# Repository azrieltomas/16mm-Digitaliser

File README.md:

# 16mm Digitaliser
A slight improvement on the [8mm Digitaliser](https://github.com/azrieltomas/8mm-Digitaliser)
This is currently a work in progress and not fully implemented.

### Design
The hardware design to capture the frames utilises a constantly running motor, and dual IR sensors to determine when sprocket perforations have passed.
As 5+ frames can fit on the digital capture, photographs are taken every 5 frames. Cropping will be acheived by automatically offsetting the crop zone and exporting to separate images.

### Parts
Parts for aligning the film and holding the sensors are from various 3D prints.

\
*Physical Parts Layout (FreeCAD)*

### Controller
Each perforation sensor has two fine tuning methods:
* Gain (affects sensor output level)
* Cutoff (affects reference level).
The gain and cutoff signals are compared with an LM741 to determine if a perforation is sensed.This is adjustable to compensate for light sections along the film edge that are not perforations, but are still picked up by the sensor.Both perforation sensors are connected by an AND gate to a counter to further filter out non-perforations on single sides of the film.

For single perforation film, a switch sets the sense2 output to always on.

Once the counter has reaches four, it triggers the camera, and resets on five via an AND gate on QA and QC.

The motor can be switched on/off via a buffer circuit. I have used a BUL128 only because I have spares, and they're the only transistor on hand that can handle the motor current. It is probably wise to put a flyback diode on the motor.

\
*Controller Design (KiCAD)*

### Audio
Audio is captured in two ways, depending on the storage method.
Digital processing can be done by any additional system.

#### Standard magnetic audio
Audio is picked up by a modified cassette tape head and amplified by an LM386 for simplicity.

#### Movietone
Audio is converted by an IR phototransistor - theoretically the same one used for the second set of perforations in dual perf film.
A BC547 amplifier boosts this to line levels.

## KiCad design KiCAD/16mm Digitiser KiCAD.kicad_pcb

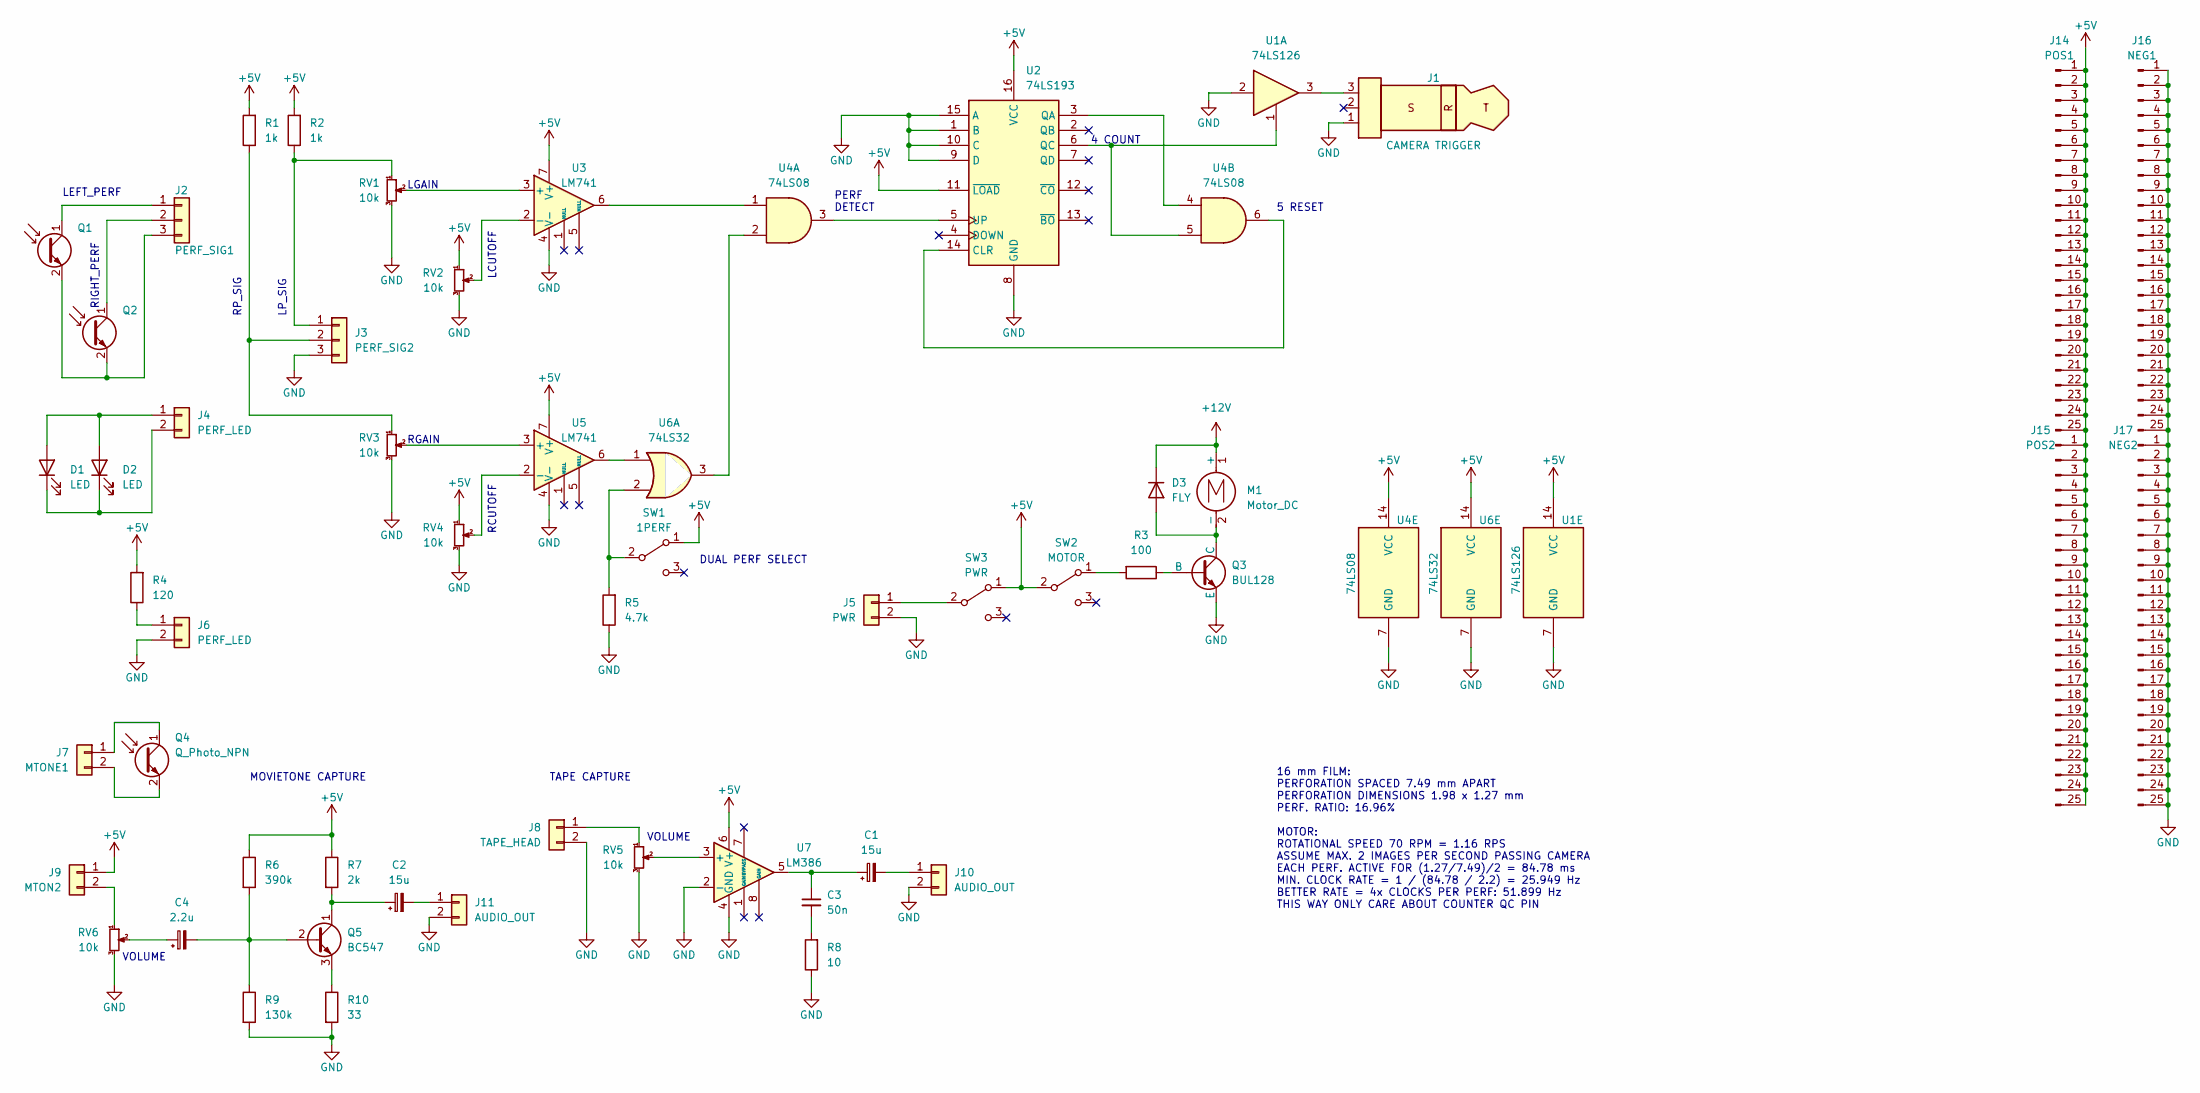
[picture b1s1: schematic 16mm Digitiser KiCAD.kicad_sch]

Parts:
C1, C2: 15u; C_Radial_D6.3mm_H5.0mm_P2.50mm
C3: 50n; C_Rect_L4.6mm_W2.0mm_P2.50mm_MKS02_FKP02
C4: 2.2u; C_Radial_D6.3mm_H5.0mm_P2.50mm
D1, D2: LED; LED_D5.0mm
D3: FLY
J1: CAMERA TRIGGER; JST_EH_B3B-EH-A_1x03_P2.50mm_Vertical
J2: PERF_SIG1; JST_EH_B3B-EH-A_1x03_P2.50mm_Vertical
J3: PERF_SIG2; JST_EH_B3B-EH-A_1x03_P2.50mm_Vertical
J4, J6: PERF_LED; JST_EH_B2B-EH-A_1x02_P2.50mm_Vertical
J5: PWR; JST_EH_B2B-EH-A_1x02_P2.50mm_Vertical
J7: MTONE1; JST_EH_B2B-EH-A_1x02_P2.50mm_Vertical
J8: TAPE_HEAD; JST_EH_B2B-EH-A_1x02_P2.50mm_Vertical
J9: MTON2; JST_EH_B2B-EH-A_1x02_P2.50mm_Vertical
J10, J11: AUDIO_OUT; JST_EH_B2B-EH-A_1x02_P2.50mm_Vertical
J14: POS1; PinHeader_1x25_P2.54mm_Vertical
J15: POS2; PinHeader_1x25_P2.54mm_Vertical
J16: NEG1; PinHeader_1x25_P2.54mm_Vertical
J17: NEG2; PinHeader_1x25_P2.54mm_Vertical
M1: Motor_DC; JST_EH_B2B-EH-A_1x02_P2.50mm_Vertical
Q1, Q2, Q4: Q_Photo_NPN; LED_D5.0mm
Q3: BUL128; TO-220-3_Vertical
Q5: BC547; TO-92_Inline
R1, R2: 1k; R_Axial_DIN0207_L6.3mm_D2.5mm_P7.62mm_Horizontal
R3: 100; R_Axial_DIN0207_L6.3mm_D2.5mm_P7.62mm_Horizontal
R4: 120; R_Axial_DIN0207_L6.3mm_D2.5mm_P7.62mm_Horizontal
R5: 4.7k; R_Axial_DIN0207_L6.3mm_D2.5mm_P7.62mm_Horizontal
R6: 390k; R_Axial_DIN0207_L6.3mm_D2.5mm_P7.62mm_Horizontal
R7: 2k; R_Axial_DIN0207_L6.3mm_D2.5mm_P7.62mm_Horizontal
R8: 10; R_Axial_DIN0207_L6.3mm_D2.5mm_P7.62mm_Horizontal
R9: 130k; R_Axial_DIN0207_L6.3mm_D2.5mm_P7.62mm_Horizontal
R10: 33; R_Axial_DIN0207_L6.3mm_D2.5mm_P7.62mm_Horizontal
RV1, RV2, RV3, RV4: 10k; Potentiometer_ACP_CA9-V10_Vertical
RV5, RV6: 10k; Potentiometer_Alps_RK163_Single_Horizontal
SW1: 1PERF; PinSocket_1x03_P2.54mm_Vertical
SW2: MOTOR; PinSocket_1x03_P2.54mm_Vertical
SW3: PWR; PinSocket_1x03_P2.54mm_Vertical
U1: 74LS126; DIP-14_W7.62mm_Socket
U2: 74LS193; DIP-16_W7.62mm_Socket
U3, U5: LM741; DIP-8_W7.62mm_Socket
U4: 74LS08; DIP-14_W7.62mm_Socket
U6: 74LS32; DIP-14_W7.62mm_Socket
U7: LM386; DIP-8_W7.62mm_Socket

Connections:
+5V: J9.1, J14.1, J14.2, J14.3, J14.4, J14.5, J14.6, J14.7, J14.8, J14.9, J14.10, J14.11, J14.12, J14.13, J14.14, J14.15, J14.16, J14.17, J14.18, J14.19, J14.20, J14.21, J14.22, J14.23, J14.24, J14.25, J15.1, J15.2, J15.3, J15.4, J15.5, J15.6, J15.7, J15.8, J15.9, J15.10, J15.11, J15.12, J15.13, J15.14, J15.15, J15.16, J15.17, J15.18, J15.19, J15.20, J15.21, J15.22, J15.23, J15.24, J15.25, R1.2, R2.2, R4.2, R6.1, R7.1, RV2.1, RV4.1, SW1.1 (A), SW2.2 (B), SW3.1 (A), U1.14 (VCC), U2.11 (~LOAD), U2.16 (VCC), U3.7 (V+), U4.14 (VCC), U5.7 (V+), U6.14 (VCC), U7.6 (V+)
+12V: D3.1 (K), M1.1 (+)
GND: J1.1, J3.3, J5.2, J6.2, J8.2, J10.2, J11.2, J16.1, J16.2, J16.3, J16.4, J16.5, J16.6, J16.7, J16.8, J16.9, J16.10, J16.11, J16.12, J16.13, J16.14, J16.15, J16.16, J16.17, J16.18, J16.19, J16.20, J16.21, J16.22, J16.23, J16.24, J16.25, J17.1, J17.2, J17.3, J17.4, J17.5, J17.6, J17.7, J17.8, J17.9, J17.10, J17.11, J17.12, J17.13, J17.14, J17.15, J17.16, J17.17, J17.18, J17.19, J17.20, J17.21, J17.22, J17.23, J17.24, J17.25, Q3.3 (E), R5.1, R8.1, R9.2, R10.2, RV1.3, RV2.3, RV3.3, RV4.3, RV5.3, RV6.3, U1.2, U1.7 (GND), U2.1 (B), U2.8 (GND), U2.9 (D), U2.10 (C), U2.15 (A), U3.4 (V-), U4.7 (GND), U5.4 (V-), U6.7 (GND), U7.2 (-), U7.4 (GND)
unnamed: C1.1, C3.1, U7.5
unnamed: C3.2, R8.2
unnamed: C4.1, RV6.2
unnamed: D1.2 (A), D2.2 (A), J4.1
unnamed: D1.1 (K), D2.1 (K), J4.2
unnamed: J1.3, U1.3
unnamed: J2.1, Q1.1 (C)
unnamed: J2.2, Q2.1 (C)
unnamed: J2.3, Q1.2 (E), Q2.2 (E)
unnamed: J3.1, R2.1, RV1.1
unnamed: J3.2, R1.1, RV3.1
unnamed: J5.1, SW3.2 (B)
unnamed: J6.1, R4.1
unnamed: J7.1, Q4.1 (C)
unnamed: J7.2, Q4.2 (E)
unnamed: J8.1, RV5.1
unnamed: J9.2, RV6.1
unnamed: C1.2, J10.1
unnamed: C2.2, J11.1
unnamed: D3.2 (A), M1.2 (-), Q3.1 (C)
unnamed: Q3.2 (B), R3.1
unnamed: C4.2, Q5.2 (B), R6.2, R9.1
unnamed: C2.1, Q5.1 (C), R7.2
unnamed: Q5.3 (E), R10.1
unnamed: R5.2, SW1.2 (B), U6.2
unnamed: R3.2, SW2.1 (A)
unnamed: U2.14 (CLR), U4.6
unnamed: U2.3 (QA), U4.4
unnamed: U2.5 (UP), U4.3
unnamed: RV1.2, U3.3 (+)
unnamed: RV2.2, U3.2 (-)
unnamed: U3.6, U4.1
unnamed: U4.2, U6.3
unnamed: RV3.2, U5.3 (+)
unnamed: RV4.2, U5.2 (-)
unnamed: U5.6, U6.1
unnamed: RV5.2, U7.3 (+)

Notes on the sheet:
LP_SIG
LGAIN
RIGHT_PERF
4 COUNT
LEFT_PERF
RP_SIG
LCUTOFF
VOLUME
RGAIN
RCUTOFF
DUAL PERF SELECT
MOVIETONE CAPTURE
16 mm FILM: PERFORATION SPACED 7.49 mm APART PERFORATION DIMENSIONS 1.98 x 1.27 mm PERF. RATIO: 16.96% MOTOR: ROTATIONAL SPEED 70 RPM = 1.16 RPS ASSUME MAX. 2 IMAGES PER SECOND PASSING CAMERA EACH PERF. ACTIVE FOR (1.27/7.49)/2 = 84.78 ms MIN. CLOCK RATE = 1 / (84.78 / 2.2) = 25.949 Hz BETTER RATE 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
TAPE CAPTURE
PERF DETECT
5 RESET

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
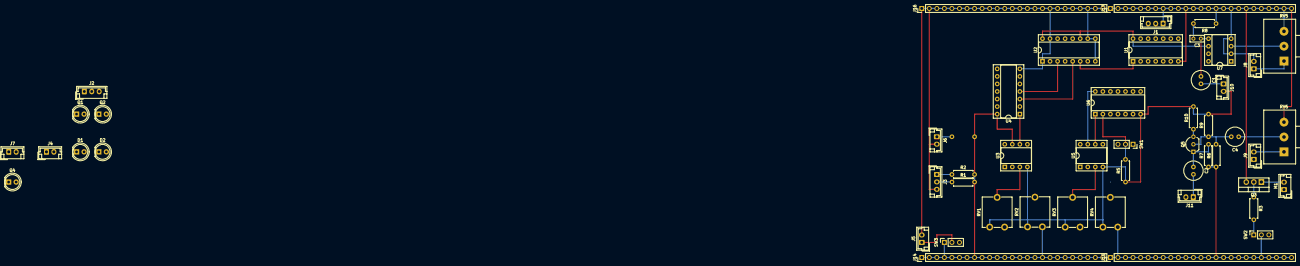
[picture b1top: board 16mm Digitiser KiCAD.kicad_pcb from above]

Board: 4 copper layers, 53 parts (1 on the bottom side), 41 nets.

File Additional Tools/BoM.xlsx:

Reference | Value | Datasheet | Footprint | Qty | DNP
C1,C2 | 15u | ~ | Capacitor_THT:C_Radial_D6.3mm_H5.0mm_P2.50mm | 2
C3 | 50n | ~ | Capacitor_THT:C_Rect_L4.6mm_W2.0mm_P2.50mm_MKS02_FKP02 | 1
C4 | 2.2u | ~ | Capacitor_THT:C_Radial_D6.3mm_H5.0mm_P2.50mm | 1
D1,D2 | LED | ~ | LED_THT:LED_D5.0mm | 2
D3 | FLY | ~ |  | 1
J1 | CAMERA TRIGGER | ~ | 2.5mm TRS Jack | 1
J2,J3 | Connector_JST:JST_EH_B3B-EH-A_1x03_P2.50mm_Vertical | ~ |  | 1
 |  |  |  | 1
J4,J6 | Connector_JST:JST_EH_B2B-EH-A_1x02_P2.50mm_Vertical | ~ |  | 2
J5,SW3 | PWR | ~ | -- mixed values -- | 2
J7 | MTONE1 | ~ | Connector_JST:JST_EH_B2B-EH-A_1x02_P2.50mm_Vertical | 1
J8 | TAPE_HEAD | ~ | Connector_JST:JST_EH_B2B-EH-A_1x02_P2.50mm_Vertical | 1
J9 | MTON2 | ~ | Connector_JST:JST_EH_B2B-EH-A_1x02_P2.50mm_Vertical | 1
J10,J11 | AUDIO_OUT | ~ | Connector_JST:JST_EH_B2B-EH-A_1x02_P2.50mm_Vertical | 2
J14 | POS1 | ~ | Connector_PinHeader_2.54mm:PinHeader_1x25_P2.54mm_Vertical | 1
J15 | POS2 | ~ | Connector_PinHeader_2.54mm:PinHeader_1x25_P2.54mm_Vertical | 1
J16 | NEG1 | ~ | Connector_PinHeader_2.54mm:PinHeader_1x25_P2.54mm_Vertical | 1
J17 | NEG2 | ~ | Connector_PinHeader_2.54mm:PinHeader_1x25_P2.54mm_Vertical | 1
M1 | Motor_DC | ~ | Connector_JST:JST_EH_B2B-EH-A_1x02_P2.50mm_Vertical | 1
Q1,Q2,Q4 | Q_Photo_NPN | ~ | LED_THT:LED_D5.0mm | 3
Q3 | BUL128 | ~ | Package_TO_SOT_THT:TO-220-3_Vertical | 1
Q5 | BC547 | https://www.onsemi.com/pub/Collateral/BC550-D.pdf | Package_TO_SOT_THT:TO-92_Inline | 1
R1,R2 | 1k | ~ | Resistor_THT:R_Axial_DIN0207_L6.3mm_D2.5mm_P7.62mm_Horizontal | 2
R3 | 100 | ~ | Resistor_THT:R_Axial_DIN0207_L6.3mm_D2.5mm_P7.62mm_Horizontal | 1
R4 | 120 | ~ | Resistor_THT:R_Axial_DIN0207_L6.3mm_D2.5mm_P7.62mm_Horizontal | 1
R5 | 4.7k | ~ | Resistor_THT:R_Axial_DIN0207_L6.3mm_D2.5mm_P7.62mm_Horizontal | 1
R6 | 390k | ~ | Resistor_THT:R_Axial_DIN0207_L6.3mm_D2.5mm_P7.62mm_Horizontal | 1
R7 | 2k | ~ | Resistor_THT:R_Axial_DIN0207_L6.3mm_D2.5mm_P7.62mm_Horizontal | 1
R8 | 10 | ~ | Resistor_THT:R_Axial_DIN0207_L6.3mm_D2.5mm_P7.62mm_Horizontal | 1
R9 | 130k | ~ | Resistor_THT:R_Axial_DIN0207_L6.3mm_D2.5mm_P7.62mm_Horizontal | 1
R10 | 33 | ~ | Resistor_THT:R_Axial_DIN0207_L6.3mm_D2.5mm_P7.62mm_Horizontal | 1
RV1,RV2,RV3,RV4,RV5,RV6 | 10k | ~ | -- mixed values -- | 6
SW1 | 1PERF | ~ | Connector_PinSocket_2.54mm:PinSocket_1x03_P2.54mm_Vertical | 1
SW2 | MOTOR | ~ | Connector_PinSocket_2.54mm:PinSocket_1x03_P2.54mm_Vertical | 1
U1 | 74LS126 | http://www.ti.com/lit/gpn/sn74LS126 | Package_DIP:DIP-14_W7.62mm_Socket | 1
U2 | 74LS193 | http://www.ti.com/lit/ds/symlink/sn74ls193.pdf | Package_DIP:DIP-16_W7.62mm_Socket | 1
U3,U5 | LM741 | http://www.ti.com/lit/ds/symlink/lm741.pdf | Package_DIP:DIP-8_W7.62mm_Socket | 2
U4 | 74LS08 | http://www.ti.com/lit/gpn/sn74LS08 | Package_DIP:DIP-14_W7.62mm_Socket | 1
U6 | 74LS32 | http://www.ti.com/lit/gpn/sn74LS32 | Package_DIP:DIP-14_W7.62mm_Socket | 1
U7 | LM386 | http://www.ti.com/lit/ds/symlink/lm386.pdf | Package_DIP:DIP-8_W7.62mm_Socket | 1

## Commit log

2024-02-29 first issue
2024-02-29 readme formatting
2024-03-01 cad designs
2024-03-01 design layout
2024-03-01 move layout to own folder
2024-03-02 3D rendering
